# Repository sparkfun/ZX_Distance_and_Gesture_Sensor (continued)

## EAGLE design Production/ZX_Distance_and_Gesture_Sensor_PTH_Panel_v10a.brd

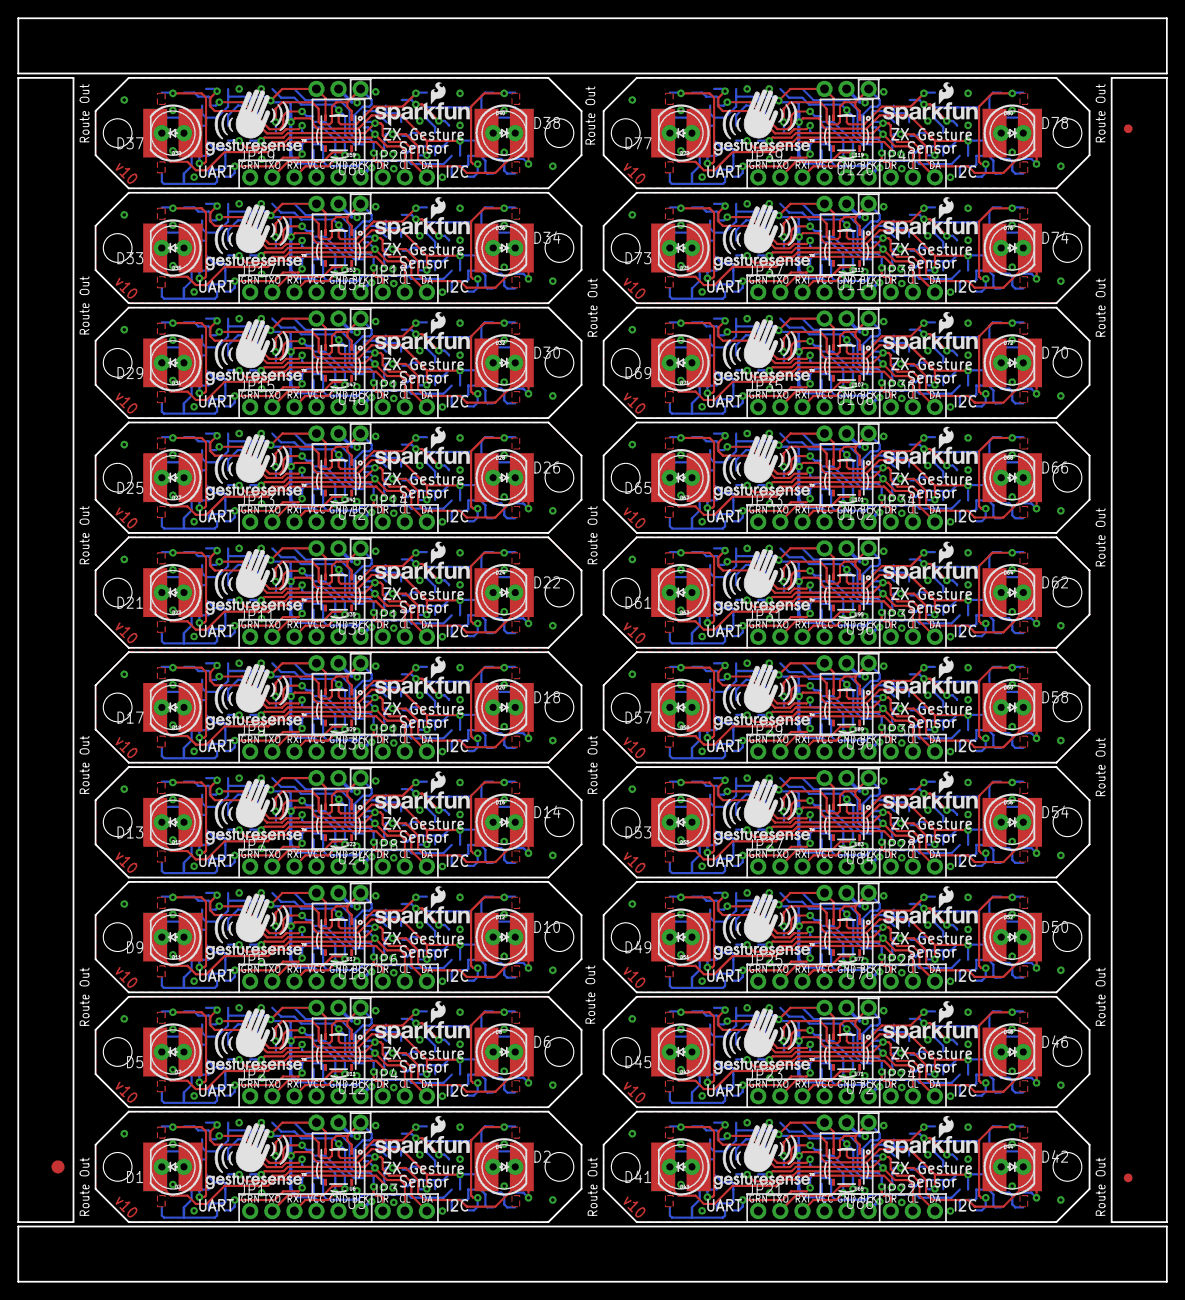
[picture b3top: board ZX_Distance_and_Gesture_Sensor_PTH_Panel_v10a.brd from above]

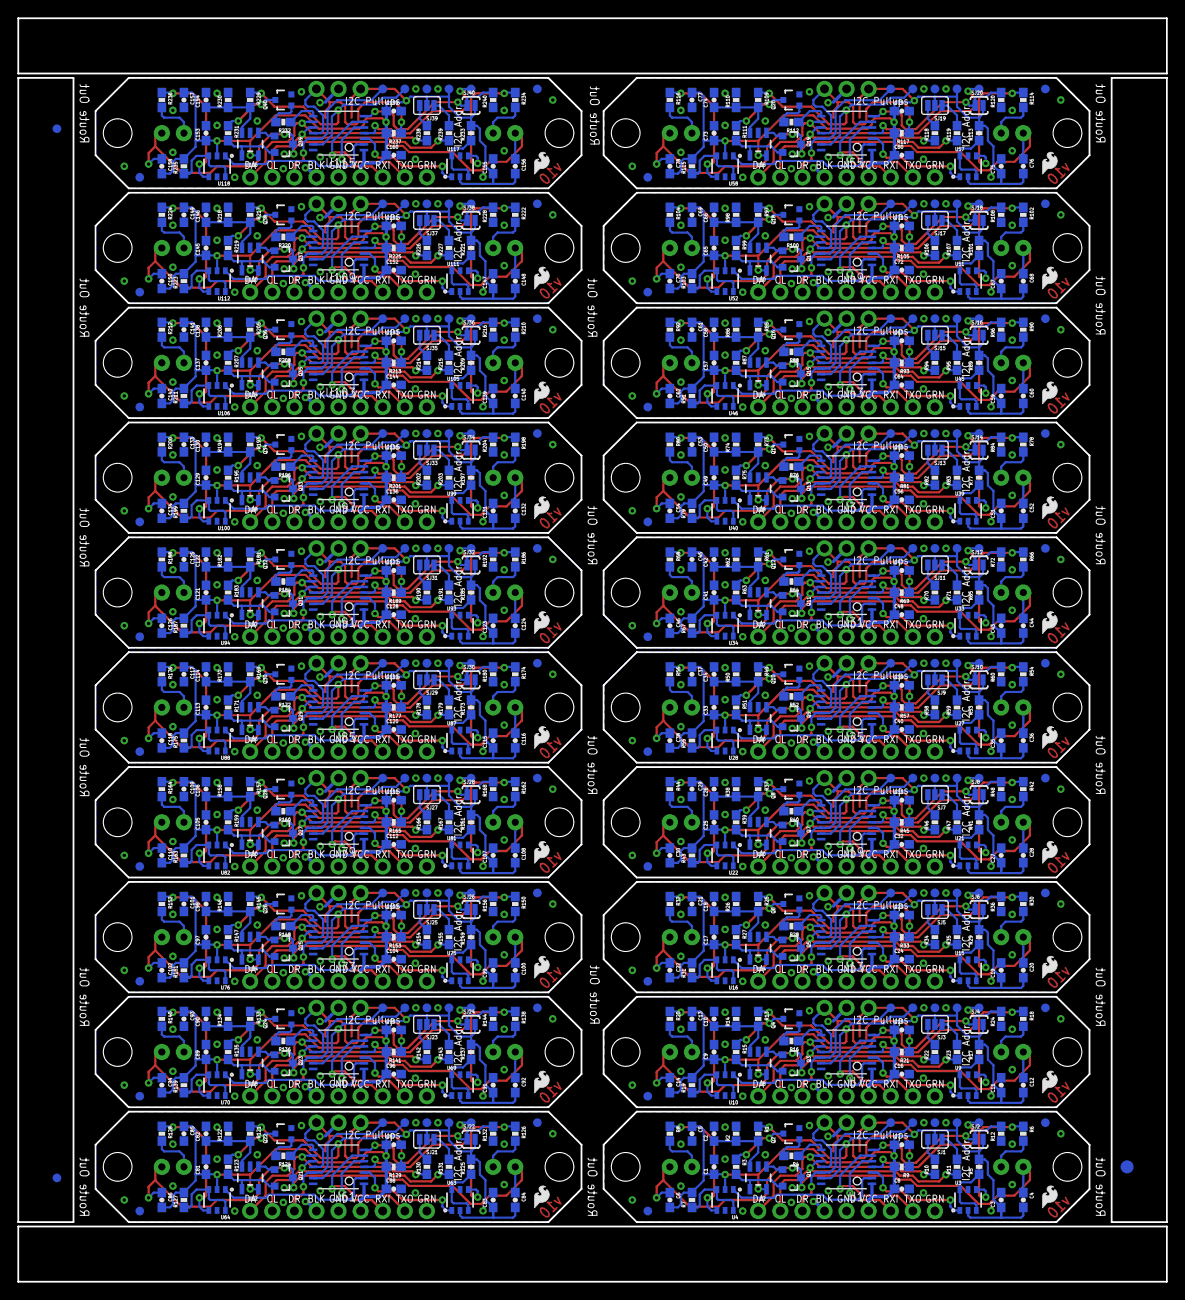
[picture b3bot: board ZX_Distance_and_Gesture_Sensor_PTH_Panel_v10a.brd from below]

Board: 2 copper layers, 132.1 x 145.3 mm, 966 parts (723 on the bottom side), 560 nets.

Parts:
C1, C3, C5, C8, C9, C11, C13, C16, C17, C19, C21, C24, C25, C27, C29, C32, C33, C35, C37, C40, C41, C43, C45, C48, C49, C51, C53, C56, C57, C59, C61, C64, C65, C67, C69, C72, C73, C75, C77, C80, C81, C83, C85, C88, C89, C91, C93, C96, C97, C99, C101, C104, C105, C107, C109, C112, C113, C115, C117, C120, C121, C123, C125, C128, C129, C131, C133, C136, C137, C139, C141, C144, C145, C147, C149, C152, C153, C155, C157, C160: 0.1uF; 0603-CAP
C2, C10, C18, C26, C34, C42, C50, C58, C66, C74, C82, C90, C98, C106, C114, C122, C130, C138, C146, C154: DNP; 0603-CAP
C4, C6, C12, C14, C20, C22, C28, C30, C36, C38, C44, C46, C52, C54, C60, C62, C68, C70, C76, C78, C84, C86, C92, C94, C100, C102, C108, C110, C116, C118, C124, C126, C132, C134, C140, C142, C148, C150, C156, C158: 10nF; 0603-CAP
C7, C15, C23, C31, C39, C47, C55, C63, C71, C79, C87, C95, C103, C111, C119, C127, C135, C143, C151, C159: 4.7uF; 0603-CAP
D1, D2, D5, D6, D9, D10, D13, D14, D17, D18, D21, D22, D25, D26, D29, D30, D33, D34, D37, D38, D41, D42, D45, D46, D49, D50, D53, D54, D57, D58, D61, D62, D65, D66, D69, D70, D73, D74, D77, D78: LED-IR-THRUTSAL6100; LED5MM
D3, D4, D7, D8, D11, D12, D15, D16, D19, D20, D23, D24, D27, D28, D31, D32, D35, D36, D39, D40, D43, D44, D47, D48, D51, D52, D55, D56, D59, D60, D63, D64, D67, D68, D71, D72, D75, D76, D79, D80: SFH4641SHORT2; SFH4641-SHORT2
E$1, E$3: FIDUCIAL-1.5X3
E$2, E$4, E$5, E$6: FIDUCIAL-1X2
FID1, FID2, FID3, FID4, FID5, FID6, FID7, FID8, FID9, FID10, FID11, FID12, FID13, FID14, FID15, FID16, FID17, FID18, FID19, FID20, FID21, FID22, FID23, FID24, FID25, FID26, FID27, FID28, FID29, FID30, FID31, FID32, FID33, FID34, FID35, FID36, FID37, FID38, FID39, FID40: FIDUCIAL1X2; FIDUCIAL-1X2
JP1, JP2, JP5, JP7, JP9, JP11, JP13, JP15, JP17, JP19, JP21, JP23, JP25, JP27, JP29, JP31, JP33, JP35, JP37, JP39: 1X06_NO_SILK
JP3, JP4, JP6, JP8, JP10, JP12, JP14, JP16, JP18, JP20, JP22, JP24, JP26, JP28, JP30, JP32, JP34, JP36, JP38, JP40: 1X03_NO_SILK
LOGO1, LOGO2, LOGO3, LOGO4, LOGO5, LOGO6, LOGO7, LOGO8, LOGO9, LOGO10, LOGO11, LOGO12, LOGO13, LOGO14, LOGO15, LOGO16, LOGO17, LOGO18, LOGO19, LOGO20: SFE_LOGO_FLAME.1_INCH; SFE_LOGO_FLAME_.1
Q1, Q3, Q5, Q7, Q9, Q11, Q13, Q15, Q17, Q19, Q21, Q23, Q25, Q27, Q29, Q31, Q33, Q35, Q37, Q39: MMBT2222A; SOT23-3
Q2, Q4, Q6, Q8, Q10, Q12, Q14, Q16, Q18, Q20, Q22, Q24, Q26, Q28, Q30, Q32, Q34, Q36, Q38, Q40: MOSFET-NCHANNEL2N7002PW; SOT323
R1, R2, R5, R7, R13, R14, R17, R19, R25, R26, R29, R31, R37, R38, R41, R43, R49, R50, R53, R55, R61, R62, R65, R67, R73, R74, R77, R79, R85, R86, R89, R91, R97, R98, R101, R103, R109, R110, R113, R115, R121, R122, R125, R127, R133, R134, R137, R139, R145, R146, R149, R151, R157, R158, R161, R163, R169, R170, R173, R175, R181, R182, R185, R187, R193, R194, R197, R199, R205, R206, R209, R211, R217, R218, R221, R223, R229, R230, R233, R235: 100k; 0603-RES
R3, R15, R27, R39, R51, R63, R75, R87, R99, R111, R123, R135, R147, R159, R171, R183, R195, R207, R219, R231: 10; 0603-RES
R4, R9, R16, R21, R28, R33, R40, R45, R52, R57, R64, R69, R76, R81, R88, R93, R100, R105, R112, R117, R124, R129, R136, R141, R148, R153, R160, R165, R172, R177, R184, R189, R196, R201, R208, R213, R220, R225, R232, R237: 1K; 0603-RES
R6, R8, R18, R20, R30, R32, R42, R44, R54, R56, R66, R68, R78, R80, R90, R92, R102, R104, R114, R116, R126, R128, R138, R140, R150, R152, R162, R164, R174, R176, R186, R188, R198, R200, R210, R212, R222, R224, R234, R236: 1; 0603-RES
R10, R11, R22, R23, R34, R35, R46, R47, R58, R59, R70, R71, R82, R83, R94, R95, R106, R107, R118, R119, R130, R131, R142, R143, R154, R155, R166, R167, R178, R179, R190, R191, R202, R203, R214, R215, R226, R227, R238, R239: 4.7K; 0603-RES
R12, R24, R36, R48, R60, R72, R84, R96, R108, R120, R132, R144, R156, R168, R180, R192, R204, R216, R228, R240: 10K; 0603-RES
SJ1, SJ3, SJ5, SJ7, SJ9, SJ11, SJ13, SJ15, SJ17, SJ19, SJ21, SJ23, SJ25, SJ27, SJ29, SJ31, SJ33, SJ35, SJ37, SJ39: JUMPER-PAD-3-NC_BY_PASTE; PAD-JUMPER-3-NC_BY_PASTE_YES_SILK_FULL_BOX
SJ2, SJ4, SJ6, SJ8, SJ10, SJ12, SJ14, SJ16, SJ18, SJ20, SJ22, SJ24, SJ26, SJ28, SJ30, SJ32, SJ34, SJ36, SJ38, SJ40: JUMPER-PAD-2-NOYES_SILK; PAD-JUMPER-2-NO_YES_SILK
STANDOFF1, STANDOFF2, STANDOFF3, STANDOFF4, STANDOFF5, STANDOFF6, STANDOFF7, STANDOFF8, STANDOFF9, STANDOFF10, STANDOFF11, STANDOFF12, STANDOFF13, STANDOFF14, STANDOFF15, STANDOFF16, STANDOFF17, STANDOFF18, STANDOFF19, STANDOFF20, STANDOFF21, STANDOFF22, STANDOFF23, STANDOFF24, STANDOFF25, STANDOFF26, STANDOFF27, STANDOFF28, STANDOFF29, STANDOFF30, STANDOFF31, STANDOFF32, STANDOFF33, STANDOFF34, STANDOFF35, STANDOFF36, STANDOFF37, STANDOFF38, STANDOFF39, STANDOFF40: STAND-OFF
TP1, TP2, TP3, TP4, TP5, TP6, TP7, TP8, TP9, TP10, TP11, TP12, TP13, TP14, TP15, TP16, TP17, TP18, TP19, TP20, TP21, TP22, TP23, TP24, TP25, TP26, TP27, TP28, TP29, TP30, TP31, TP32, TP33, TP34, TP35, TP36, TP37, TP38, TP39, TP40, TP41, TP42, TP43, TP44, TP45, TP46, TP47, TP48, TP49, TP50, TP51, TP52, TP53, TP54, TP55, TP56, TP57, TP58, TP59, TP60, TP61, TP62, TP63, TP64, TP65, TP66, TP67, TP68, TP69, TP70, TP71, TP72, TP73, TP74, TP75, TP76, TP77, TP78, TP79, TP80, TP81, TP82, TP83, TP84, TP85, TP86, TP87, TP88, TP89, TP90, TP91, TP92, TP93, TP94, TP95, TP96, TP97, TP98, TP99, TP100: TEST-POINT3X4; PAD.03X.04
U1, U7, U13, U19, U25, U31, U37, U43, U49, U55, U61, U67, U73, U79, U85, U91, U97, U103, U109, U115: PIC16F1823-14PINTSSOP; TSSOP14
U2, U8, U14, U20, U26, U32, U38, U44, U50, U56, U62, U68, U74, U80, U86, U92, U98, U104, U110, U116: MCP6021T-E/OT; SOT23-5
U3, U4, U9, U10, U15, U16, U21, U22, U27, U28, U33, U34, U39, U40, U45, U46, U51, U52, U57, U58, U63, U64, U69, U70, U75, U76, U81, U82, U87, U88, U93, U94, U99, U100, U105, U106, U111, U112, U117, U118: DMC2700UDM; SOT26
U5, U12, U18, U24, U30, U36, U42, U48, U54, U60, U66, U72, U78, U84, U90, U96, U102, U108, U114, U120: BRM-2A18VERT; BRM-2508_VERT
U6, U11, U17, U23, U29, U35, U41, U47, U53, U59, U65, U71, U77, U83, U89, U95, U101, U107, U113, U119: TSOP57238TT1; TSOP572
U$1, U$3, U$5, U$7, U$9, U$11, U$13, U$15, U$17, U$19, U$21, U$23, U$25, U$27, U$29, U$31, U$33, U$35, U$37, U$39: SFE_LOGO_NAME_FLAME.1_INCH; SFE_LOGO_NAME_FLAME_.1
U$2, U$4, U$6, U$8, U$10, U$12, U$14, U$16, U$18, U$20, U$22, U$24, U$26, U$28, U$30, U$32, U$34, U$36, U$38, U$40: GESTURESENSE_LOGOSTEXT; GESTURESENSE_TEXT

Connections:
CARRIER: R4.1, U1.8
CARRIER1: R16.1, U7.8
CARRIER2: R28.1, U13.8
CARRIER3: R40.1, U19.8
CARRIER4: R52.1, U25.8
CARRIER5: R64.1, U31.8
CARRIER6: R76.1, U37.8
CARRIER7: R88.1, U43.8
CARRIER8: R100.1, U49.8
CARRIER9: R112.1, U55.8
CARRIER10: R124.1, U61.8
CARRIER11: R136.1, U67.8
CARRIER12: R148.1, U73.8
CARRIER13: R160.1, U79.8
CARRIER14: R172.1, U85.8
CARRIER15: R184.1, U91.8
CARRIER16: R196.1, U97.8
CARRIER17: R208.1, U103.8
CARRIER18: R220.1, U109.8
CARRIER19: R232.1, U115.8
COMMON: C4.1, C6.1, D1.K, D2.K, D3.C, D4.C, Q1.3
COMMON1: C12.1, C14.1, D5.K, D6.K, D7.C, D8.C, Q3.3
COMMON2: C20.1, C22.1, D9.K, D10.K, D11.C, D12.C, Q5.3
COMMON3: C28.1, C30.1, D13.K, D14.K, D15.C, D16.C, Q7.3
COMMON4: C36.1, C38.1, D17.K, D18.K, D19.C, D20.C, Q9.3
COMMON5: C44.1, C46.1, D21.K, D22.K, D23.C, D24.C, Q11.3
COMMON6: C52.1, C54.1, D25.K, D26.K, D27.C, D28.C, Q13.3
COMMON7: C60.1, C62.1, D29.K, D30.K, D31.C, D32.C, Q15.3
COMMON8: C68.1, C70.1, D33.K, D34.K, D35.C, D36.C, Q17.3
COMMON9: C76.1, C78.1, D37.K, D38.K, D39.C, D40.C, Q19.3
COMMON10: C84.1, C86.1, D41.K, D42.K, D43.C, D44.C, Q21.3
COMMON11: C92.1, C94.1, D45.K, D46.K, D47.C, D48.C, Q23.3
COMMON12: C100.1, C102.1, D49.K, D50.K, D51.C, D52.C, Q25.3
COMMON13: C108.1, C110.1, D53.K, D54.K, D55.C, D56.C, Q27.3
COMMON14: C116.1, C118.1, D57.K, D58.K, D59.C, D60.C, Q29.3
COMMON15: C124.1, C126.1, D61.K, D62.K, D63.C, D64.C, Q31.3
COMMON16: C132.1, C134.1, D65.K, D66.K, D67.C, D68.C, Q33.3
COMMON17: C140.1, C142.1, D69.K, D70.K, D71.C, D72.C, Q35.3
COMMON18: C148.1, C150.1, D73.K, D74.K, D75.C, D76.C, Q37.3
COMMON19: C156.1, C158.1, D77.K, D78.K, D79.C, D80.C, Q39.3
EM1: U1.3, U3.G1
EM2: U1.2, U4.G1
EM3: U7.3, U9.G1
EM4: U7.2, U10.G1
EM5: U13.3, U15.G1
EM6: U13.2, U16.G1
EM7: U19.3, U21.G1
EM8: U19.2, U22.G1
EM9: U25.3, U27.G1
EM10: U25.2, U28.G1
EM11: U31.3, U33.G1
EM12: U31.2, U34.G1
EM13: U37.3, U39.G1
EM14: U37.2, U40.G1
EM15: U43.3, U45.G1
EM16: U43.2, U46.G1
EM17: U49.3, U51.G1
EM18: U49.2, U52.G1
EM19: U55.3, U57.G1
EM20: U55.2, U58.G1
EM21: U61.3, U63.G1
EM22: U61.2, U64.G1
EM23: U67.3, U69.G1
EM24: U67.2, U70.G1
EM25: U73.3, U75.G1
EM26: U73.2, U76.G1
EM27: U79.3, U81.G1
EM28: U79.2, U82.G1
EM29: U85.3, U87.G1
EM30: U85.2, U88.G1
EM31: U91.3, U93.G1
EM32: U91.2, U94.G1
EM33: U97.3, U99.G1
EM34: U97.2, U100.G1
EM35: U103.3, U105.G1
EM36: U103.2, U106.G1
EM37: U109.3, U111.G1
EM38: U109.2, U112.G1
EM39: U115.3, U117.G1
EM40: U115.2, U118.G1
GND: C1.2, C2.2, C3.2, C5.2, C7.2, C8.2, JP1.5, JP1.6, Q2.2, R2.2, R12.1, TP2.P$1, U1.14, U2.2, U3.S1, U4.S1, U5.2, U6.6, U6.8
GND1: C9.2, C10.2, C11.2, C13.2, C15.2, C16.2, JP2.5, JP2.6, Q4.2, R14.2, R24.1, TP7.P$1, U7.14, U8.2, U9.S1, U10.S1, U11.6, U11.8, U12.2
GND2: C17.2, C18.2, C19.2, C21.2, C23.2, C24.2, JP5.5, JP5.6, Q6.2, R26.2, R36.1, TP12.P$1, U13.14, U14.2, U15.S1, U16.S1, U17.6, U17.8, U18.2
GND3: C25.2, C26.2, C27.2, C29.2, C31.2, C32.2, JP7.5, JP7.6, Q8.2, R38.2, R48.1, TP17.P$1, U19.14, U20.2, U21.S1, U22.S1, U23.6, U23.8, U24.2
GND4: C33.2, C34.2, C35.2, C37.2, C39.2, C40.2, JP9.5, JP9.6, Q10.2, R50.2, R60.1, TP22.P$1, U25.14, U26.2, U27.S1, U28.S1, U29.6, U29.8, U30.2
GND5: C41.2, C42.2, C43.2, C45.2, C47.2, C48.2, JP11.5, JP11.6, Q12.2, R62.2, R72.1, TP27.P$1, U31.14, U32.2, U33.S1, U34.S1, U35.6, U35.8, U36.2
GND6: C49.2, C50.2, C51.2, C53.2, C55.2, C56.2, JP13.5, JP13.6, Q14.2, R74.2, R84.1, TP32.P$1, U37.14, U38.2, U39.S1, U40.S1, U41.6, U41.8, U42.2
GND7: C57.2, C58.2, C59.2, C61.2, C63.2, C64.2, JP15.5, JP15.6, Q16.2, R86.2, R96.1, TP37.P$1, U43.14, U44.2, U45.S1, U46.S1, U47.6, U47.8, U48.2
GND8: C65.2, C66.2, C67.2, C69.2, C71.2, C72.2, JP17.5, JP17.6, Q18.2, R98.2, R108.1, TP42.P$1, U49.14, U50.2, U51.S1, U52.S1, U53.6, U53.8, U54.2
GND9: C73.2, C74.2, C75.2, C77.2, C79.2, C80.2, JP19.5, JP19.6, Q20.2, R110.2, R120.1, TP47.P$1, U55.14, U56.2, U57.S1, U58.S1, U59.6, U59.8, U60.2
GND10: C81.2, C82.2, C83.2, C85.2, C87.2, C88.2, JP21.5, JP21.6, Q22.2, R122.2, R132.1, TP52.P$1, U61.14, U62.2, U63.S1, U64.S1, U65.6, U65.8, U66.2
GND11: C89.2, C90.2, C91.2, C93.2, C95.2, C96.2, JP23.5, JP23.6, Q24.2, R134.2, R144.1, TP57.P$1, U67.14, U68.2, U69.S1, U70.S1, U71.6, U71.8, U72.2
GND12: C97.2, C98.2, C99.2, C101.2, C103.2, C104.2, JP25.5, JP25.6, Q26.2, R146.2, R156.1, TP62.P$1, U73.14, U74.2, U75.S1, U76.S1, U77.6, U77.8, U78.2
GND13: C105.2, C106.2, C107.2, C109.2, C111.2, C112.2, JP27.5, JP27.6, Q28.2, R158.2, R168.1, TP67.P$1, U79.14, U80.2, U81.S1, U82.S1, U83.6, U83.8, U84.2
GND14: C113.2, C114.2, C115.2, C117.2, C119.2, C120.2, JP29.5, JP29.6, Q30.2, R170.2, R180.1, TP72.P$1, U85.14, U86.2, U87.S1, U88.S1, U89.6, U89.8, U90.2
GND15: C121.2, C122.2, C123.2, C125.2, C127.2, C128.2, JP31.5, JP31.6, Q32.2, R182.2, R192.1, TP77.P$1, U91.14, U92.2, U93.S1, U94.S1, U95.6, U95.8, U96.2
GND16: C129.2, C130.2, C131.2, C133.2, C135.2, C136.2, JP33.5, JP33.6, Q34.2, R194.2, R204.1, TP82.P$1, U97.14, U98.2, U99.S1, U100.S1, U101.6, U101.8, U102.2
GND17: C137.2, C138.2, C139.2, C141.2, C143.2, C144.2, JP35.5, JP35.6, Q36.2, R206.2, R216.1, TP87.P$1, U103.14, U104.2, U105.S1, U106.S1, U107.6, U107.8, U108.2
GND18: C145.2, C146.2, C147.2, C149.2, C151.2, C152.2, JP37.5, JP37.6, Q38.2, R218.2, R228.1, TP92.P$1, U109.14, U110.2, U111.S1, U112.S1, U113.6, U113.8, U114.2
GND19: C153.2, C154.2, C155.2, C157.2, C159.2, C160.2, JP39.5, JP39.6, Q40.2, R230.2, R240.1, TP97.P$1, U115.14, U116.2, U117.S1, U118.S1, U119.6, U119.8, U120.2
I2C_ADDR: R12.2, SJ2.1, U1.7
I2C_ADDR1: R24.2, SJ4.1, U7.7
I2C_ADDR2: R36.2, SJ6.1, U13.7
I2C_ADDR3: R48.2, SJ8.1, U19.7
I2C_ADDR4: R60.2, SJ10.1, U25.7
I2C_ADDR5: R72.2, SJ12.1, U31.7
I2C_ADDR6: R84.2, SJ14.1, U37.7
I2C_ADDR7: R96.2, SJ16.1, U43.7
I2C_ADDR8: R108.2, SJ18.1, U49.7
I2C_ADDR9: R120.2, SJ20.1, U55.7
I2C_ADDR10: R132.2, SJ22.1, U61.7
I2C_ADDR11: R144.2, SJ24.1, U67.7
I2C_ADDR12: R156.2, SJ26.1, U73.7
I2C_ADDR13: R168.2, SJ28.1, U79.7
I2C_ADDR14: R180.2, SJ30.1, U85.7
I2C_ADDR15: R192.2, SJ32.1, U91.7
I2C_ADDR16: R204.2, SJ34.1, U97.7
I2C_ADDR17: R216.2, SJ36.1, U103.7
I2C_ADDR18: R228.2, SJ38.1, U109.7
I2C_ADDR19: R240.2, SJ40.1, U115.7
I2C_SCL: JP3.2, R11.1, U1.10
I2C_SCL1: JP4.2, R23.1, U7.10
I2C_SCL2: JP6.2, R35.1, U13.10
I2C_SCL3: JP8.2, R47.1, U19.10
I2C_SCL4: JP10.2, R59.1, U25.10
I2C_SCL5: JP12.2, R71.1, U31.10
I2C_SCL6: JP14.2, R83.1, U37.10
I2C_SCL7: JP16.2, R95.1, U43.10
I2C_SCL8: JP18.2, R107.1, U49.10
I2C_SCL9: JP20.2, R119.1, U55.10
I2C_SCL10: JP22.2, R131.1, U61.10
I2C_SCL11: JP24.2, R143.1, U67.10
I2C_SCL12: JP26.2, R155.1, U73.10
I2C_SCL13: JP28.2, R167.1, U79.10
I2C_SCL14: JP30.2, R179.1, U85.10
I2C_SCL15: JP32.2, R191.1, U91.10
I2C_SCL16: JP34.2, R203.1, U97.10
I2C_SCL17: JP36.2, R215.1, U103.10
I2C_SCL18: JP38.2, R227.1, U109.10
I2C_SCL19: JP40.2, R239.1, U115.10
I2C_SDA: JP3.3, R10.1, U1.9
I2C_SDA1: JP4.3, R22.1, U7.9
I2C_SDA2: JP6.3, R34.1, U13.9
I2C_SDA3: JP8.3, R46.1, U19.9
I2C_SDA4: JP10.3, R58.1, U25.9
I2C_SDA5: JP12.3, R70.1, U31.9
I2C_SDA6: JP14.3, R82.1, U37.9
I2C_SDA7: JP16.3, R94.1, U43.9
I2C_SDA8: JP18.3, R106.1, U49.9
I2C_SDA9: JP20.3, R118.1, U55.9
I2C_SDA10: JP22.3, R130.1, U61.9
I2C_SDA11: JP24.3, R142.1, U67.9
I2C_SDA12: JP26.3, R154.1, U73.9
I2C_SDA13: JP28.3, R166.1, U79.9
I2C_SDA14: JP30.3, R178.1, U85.9
I2C_SDA15: JP32.3, R190.1, U91.9
I2C_SDA16: JP34.3, R202.1, U97.9
I2C_SDA17: JP36.3, R214.1, U103.9
I2C_SDA18: JP38.3, R226.1, U109.9
I2C_SDA19: JP40.3, R238.1, U115.9
ICSPCLK/DATA_RDY: JP3.1, TP4.P$1, U1.12
ICSPCLK/DATA_RDY1: JP4.1, TP9.P$1, U7.12
ICSPCLK/DATA_RDY2: JP6.1, TP14.P$1, U13.12
ICSPCLK/DATA_RDY3: JP8.1, TP19.P$1, U19.12
ICSPCLK/DATA_RDY4: JP10.1, TP24.P$1, U25.12
ICSPCLK/DATA_RDY5: JP12.1, TP29.P$1, U31.12
ICSPCLK/DATA_RDY6: JP14.1, TP34.P$1, U37.12
ICSPCLK/DATA_RDY7: JP16.1, TP39.P$1, U43.12
ICSPCLK/DATA_RDY8: JP18.1, TP44.P$1, U49.12
ICSPCLK/DATA_RDY9: JP20.1, TP49.P$1, U55.12
ICSPCLK/DATA_RDY10: JP22.1, TP54.P$1, U61.12
ICSPCLK/DATA_RDY11: JP24.1, TP59.P$1, U67.12
ICSPCLK/DATA_RDY12: JP26.1, TP64.P$1, U73.12
ICSPCLK/DATA_RDY13: JP28.1, TP69.P$1, U79.12
ICSPCLK/DATA_RDY14: JP30.1, TP74.P$1, U85.12
ICSPCLK/DATA_RDY15: JP32.1, TP79.P$1, U91.12
ICSPCLK/DATA_RDY16: JP34.1, TP84.P$1, U97.12
ICSPCLK/DATA_RDY17: JP36.1, TP89.P$1, U103.12
ICSPCLK/DATA_RDY18: JP38.1, TP94.P$1, U109.12
ICSPCLK/DATA_RDY19: JP40.1, TP99.P$1, U115.12
ICSPDAT/DACOUT: R1.1, TP5.P$1, U1.13
ICSPDAT/DACOUT1: R13.1, TP10.P$1, U7.13
ICSPDAT/DACOUT2: R25.1, TP15.P$1, U13.13
ICSPDAT/DACOUT3: R37.1, TP20.P$1, U19.13
ICSPDAT/DACOUT4: R49.1, TP25.P$1, U25.13
ICSPDAT/DACOUT5: R61.1, TP30.P$1, U31.13
ICSPDAT/DACOUT6: R73.1, TP35.P$1, U37.13
ICSPDAT/DACOUT7: R85.1, TP40.P$1, U43.13
ICSPDAT/DACOUT8: R97.1, TP45.P$1, U49.13
ICSPDAT/DACOUT9: R109.1, TP50.P$1, U55.13
ICSPDAT/DACOUT10: R121.1, TP55.P$1, U61.13
ICSPDAT/DACOUT11: R133.1, TP60.P$1, U67.13
ICSPDAT/DACOUT12: R145.1, TP65.P$1, U73.13
ICSPDAT/DACOUT13: R157.1, TP70.P$1, U79.13
ICSPDAT/DACOUT14: R169.1, TP75.P$1, U85.13
ICSPDAT/DACOUT15: R181.1, TP80.P$1, U91.13
ICSPDAT/DACOUT16: R193.1, TP85.P$1, U97.13
ICSPDAT/DACOUT17: R205.1, TP90.P$1, U103.13
ICSPDAT/DACOUT18: R217.1, TP95.P$1, U109.13
ICSPDAT/DACOUT19: R229.1, TP100.P$1, U115.13
MCLR: TP3.P$1, U1.4
MCLR1: TP8.P$1, U7.4
MCLR2: TP13.P$1, U13.4
MCLR3: TP18.P$1, U19.4
MCLR4: TP23.P$1, U25.4
MCLR5: TP28.P$1, U31.4
MCLR6: TP33.P$1, U37.4
MCLR7: TP38.P$1, U43.4
MCLR8: TP43.P$1, U49.4
MCLR9: TP48.P$1, U55.4
MCLR10: TP53.P$1, U61.4
MCLR11: TP58.P$1, U67.4
MCLR12: TP63.P$1, U73.4
MCLR13: TP68.P$1, U79.4
MCLR14: TP73.P$1, U85.4
MCLR15: TP78.P$1, U91.4
MCLR16: TP83.P$1, U97.4
MCLR17: TP88.P$1, U103.4
MCLR18: TP93.P$1, U109.4
MCLR19: TP98.P$1, U115.4
unnamed: C2.1, R1.2, R2.1, U2.3
unnamed: Q1.2, R3.2, U2.4
unnamed: Q1.1, U2.1
unnamed: Q2.3, R3.1
unnamed: Q2.1, R4.2
unnamed: R6.1, U3.D2
unnamed: D1.A, D3.A, R6.2
unnamed: R5.1, U3.D1, U3.G2
unnamed: R7.1, U4.D1, U4.G2
unnamed: R10.2, SJ1.3
unnamed: R8.1, U4.D2
unnamed: D2.A, D4.A, R8.2
unnamed: R11.2, SJ1.1
unnamed: C10.1, R13.2, R14.1, U8.3
unnamed: Q3.1, U8.1
unnamed: Q4.3, R15.1
unnamed: Q4.1, R16.2
unnamed: Q3.2, R15.2, U8.4
unnamed: R18.1, U9.D2
unnamed: D5.A, D7.A, R18.2
unnamed: R17.1, U9.D1, U9.G2
unnamed: R19.1, U10.D1, U10.G2
unnamed: R20.1, U10.D2
unnamed: D6.A, D8.A, R20.2
unnamed: R22.2, SJ3.3
unnamed: R23.2, SJ3.1
unnamed: C18.1, R25.2, R26.1, U14.3
unnamed: Q5.1, U14.1
unnamed: Q6.3, R27.1
unnamed: Q6.1, R28.2
unnamed: Q5.2, R27.2, U14.4
unnamed: R30.1, U15.D2
unnamed: D9.A, D11.A, R30.2
unnamed: R29.1, U15.D1, U15.G2
unnamed: R31.1, U16.D1, U16.G2
unnamed: R32.1, U16.D2
unnamed: D10.A, D12.A, R32.2
unnamed: R34.2, SJ5.3
unnamed: R35.2, SJ5.1
unnamed: C26.1, R37.2, R38.1, U20.3
unnamed: Q7.1, U20.1
unnamed: Q8.3, R39.1
unnamed: Q8.1, R40.2
unnamed: Q7.2, R39.2, U20.4
unnamed: R42.1, U21.D2
unnamed: D13.A, D15.A, R42.2
unnamed: R41.1, U21.D1, U21.G2
unnamed: R43.1, U22.D1, U22.G2
unnamed: R44.1, U22.D2
unnamed: D14.A, D16.A, R44.2
unnamed: R46.2, SJ7.3
unnamed: R47.2, SJ7.1
unnamed: C34.1, R49.2, R50.1, U26.3
unnamed: Q9.1, U26.1
unnamed: Q10.3, R51.1
unnamed: Q10.1, R52.2
unnamed: Q9.2, R51.2, U26.4
unnamed: R54.1, U27.D2
unnamed: D17.A, D19.A, R54.2
unnamed: R53.1, U27.D1, U27.G2
unnamed: R55.1, U28.D1, U28.G2
unnamed: R56.1, U28.D2
unnamed: D18.A, D20.A, R56.2
unnamed: R58.2, SJ9.3
unnamed: R59.2, SJ9.1
unnamed: C42.1, R61.2, R62.1, U32.3
unnamed: Q11.1, U32.1
unnamed: Q12.3, R63.1
unnamed: Q12.1, R64.2
unnamed: Q11.2, R63.2, U32.4
unnamed: R66.1, U33.D2
unnamed: D21.A, D23.A, R66.2
unnamed: R65.1, U33.D1, U33.G2
unnamed: R67.1, U34.D1, U34.G2
unnamed: R68.1, U34.D2
unnamed: D22.A, D24.A, R68.2
unnamed: R70.2, SJ11.3
unnamed: R71.2, SJ11.1
unnamed: C50.1, R73.2, R74.1, U38.3
unnamed: Q13.1, U38.1
unnamed: Q14.3, R75.1
unnamed: Q14.1, R76.2
unnamed: Q13.2, R75.2, U38.4
unnamed: R78.1, U39.D2
unnamed: D25.A, D27.A, R78.2
unnamed: R77.1, U39.D1, U39.G2
unnamed: R79.1, U40.D1, U40.G2
unnamed: R80.1, U40.D2
unnamed: D26.A, D28.A, R80.2
unnamed: R82.2, SJ13.3
unnamed: R83.2, SJ13.1
unnamed: C58.1, R85.2, R86.1, U44.3
unnamed: Q15.1, U44.1
unnamed: Q16.3, R87.1
unnamed: Q16.1, R88.2
unnamed: Q15.2, R87.2, U44.4
unnamed: R90.1, U45.D2
unnamed: D29.A, D31.A, R90.2
unnamed: R89.1, U45.D1, U45.G2
unnamed: R91.1, U46.D1, U46.G2
unnamed: R92.1, U46.D2
unnamed: D30.A, D32.A, R92.2
unnamed: R94.2, SJ15.3
unnamed: R95.2, SJ15.1
unnamed: C66.1, R97.2, R98.1, U50.3
unnamed: Q17.1, U50.1
unnamed: Q18.3, R99.1
unnamed: Q18.1, R100.2
unnamed: Q17.2, R99.2, U50.4
unnamed: R102.1, U51.D2
unnamed: D33.A, D35.A, R102.2
unnamed: R101.1, U51.D1, U51.G2
unnamed: R103.1, U52.D1, U52.G2
unnamed: R104.1, U52.D2
unnamed: D34.A, D36.A, R104.2
unnamed: R106.2, SJ17.3
unnamed: R107.2, SJ17.1
unnamed: C74.1, R109.2, R110.1, U56.3
unnamed: Q19.1, U56.1
unnamed: Q20.3, R111.1
unnamed: Q20.1, R112.2
unnamed: Q19.2, R111.2, U56.4
unnamed: R114.1, U57.D2
unnamed: D37.A, D39.A, R114.2
unnamed: R113.1, U57.D1, U57.G2
unnamed: R115.1, U58.D1, U58.G2
unnamed: R116.1, U58.D2
unnamed: D38.A, D40.A, R116.2
unnamed: R118.2, SJ19.3
unnamed: R119.2, SJ19.1
unnamed: C82.1, R121.2, R122.1, U62.3
unnamed: Q21.1, U62.1
unnamed: Q22.3, R123.1
unnamed: Q22.1, R124.2
unnamed: Q21.2, R123.2, U62.4
unnamed: R126.1, U63.D2
unnamed: D41.A, D43.A, R126.2
unnamed: R125.1, U63.D1, U63.G2
unnamed: R127.1, U64.D1, U64.G2
unnamed: R128.1, U64.D2
unnamed: D42.A, D44.A, R128.2
unnamed: R130.2, SJ21.3
unnamed: R131.2, SJ21.1
unnamed: C90.1, R133.2, R134.1, U68.3
unnamed: Q23.1, U68.1
unnamed: Q24.3, R135.1
unnamed: Q24.1, R136.2
unnamed: Q23.2, R135.2, U68.4
unnamed: R138.1, U69.D2
unnamed: D45.A, D47.A, R138.2
unnamed: R137.1, U69.D1, U69.G2
unnamed: R139.1, U70.D1, U70.G2
unnamed: R140.1, U70.D2
unnamed: D46.A, D48.A, R140.2
unnamed: R142.2, SJ23.3
unnamed: R143.2, SJ23.1
unnamed: C98.1, R145.2, R146.1, U74.3
unnamed: Q25.1, U74.1
unnamed: Q26.3, R147.1
unnamed: Q26.1, R148.2
unnamed: Q25.2, R147.2, U74.4
unnamed: R150.1, U75.D2
unnamed: D49.A, D51.A, R150.2
unnamed: R149.1, U75.D1, U75.G2
unnamed: R151.1, U76.D1, U76.G2
unnamed: R152.1, U76.D2
unnamed: D50.A, D52.A, R152.2
unnamed: R154.2, SJ25.3
unnamed: R155.2, SJ25.1
unnamed: C106.1, R157.2, R158.1, U80.3
unnamed: Q27.1, U80.1
unnamed: Q28.3, R159.1
unnamed: Q28.1, R160.2
unnamed: Q27.2, R159.2, U80.4
unnamed: R162.1, U81.D2
unnamed: D53.A, D55.A, R162.2
unnamed: R161.1, U81.D1, U81.G2
unnamed: R163.1, U82.D1, U82.G2
unnamed: R164.1, U82.D2
unnamed: D54.A, D56.A, R164.2
unnamed: R166.2, SJ27.3
unnamed: R167.2, SJ27.1
unnamed: C114.1, R169.2, R170.1, U86.3
unnamed: Q29.1, U86.1
unnamed: Q30.3, R171.1
unnamed: Q30.1, R172.2
unnamed: Q29.2, R171.2, U86.4
unnamed: R174.1, U87.D2
unnamed: D57.A, D59.A, R174.2
unnamed: R173.1, U87.D1, U87.G2
unnamed: R175.1, U88.D1, U88.G2
unnamed: R176.1, U88.D2
unnamed: D58.A, D60.A, R176.2
unnamed: R178.2, SJ29.3
unnamed: R179.2, SJ29.1
unnamed: C122.1, R181.2, R182.1, U92.3
unnamed: Q31.1, U92.1
unnamed: Q32.3, R183.1
unnamed: Q32.1, R184.2
unnamed: Q31.2, R183.2, U92.4
unnamed: R186.1, U93.D2
unnamed: D61.A, D63.A, R186.2
unnamed: R185.1, U93.D1, U93.G2
unnamed: R187.1, U94.D1, U94.G2
unnamed: R188.1, U94.D2
unnamed: D62.A, D64.A, R188.2
unnamed: R190.2, SJ31.3
unnamed: R191.2, SJ31.1
unnamed: C130.1, R193.2, R194.1, U98.3
unnamed: Q33.1, U98.1
unnamed: Q34.3, R195.1
unnamed: Q34.1, R196.2
unnamed: Q33.2, R195.2, U98.4
unnamed: R198.1, U99.D2
unnamed: D65.A, D67.A, R198.2
unnamed: R197.1, U99.D1, U99.G2
unnamed: R199.1, U100.D1, U100.G2
unnamed: R200.1, U100.D2
unnamed: D66.A, D68.A, R200.2
unnamed: R202.2, SJ33.3
unnamed: R203.2, SJ33.1
unnamed: C138.1, R205.2, R206.1, U104.3
unnamed: Q35.1, U104.1
unnamed: Q36.3, R207.1
unnamed: Q36.1, R208.2
unnamed: Q35.2, R207.2, U104.4
unnamed: R210.1, U105.D2
unnamed: D69.A, D71.A, R210.2
unnamed: R209.1, U105.D1, U105.G2
unnamed: R211.1, U106.D1, U106.G2
unnamed: R212.1, U106.D2
unnamed: D70.A, D72.A, R212.2
unnamed: R214.2, SJ35.3
unnamed: R215.2, SJ35.1
unnamed: C146.1, R217.2, R218.1, U110.3
unnamed: Q37.1, U110.1
unnamed: Q38.3, R219.1
unnamed: Q38.1, R220.2
unnamed: Q37.2, R219.2, U110.4
unnamed: R222.1, U111.D2
unnamed: D73.A, D75.A, R222.2
unnamed: R221.1, U111.D1, U111.G2
unnamed: R223.1, U112.D1, U112.G2
unnamed: R224.1, U112.D2
unnamed: D74.A, D76.A, R224.2
unnamed: R226.2, SJ37.3
unnamed: R227.2, SJ37.1
unnamed: C154.1, R229.2, R230.1, U116.3
unnamed: Q39.1, U116.1
unnamed: Q40.3, R231.1
unnamed: Q40.1, R232.2
unnamed: Q39.2, R231.2, U116.4
unnamed: R234.1, U117.D2
unnamed: D77.A, D79.A, R234.2
unnamed: R233.1, U117.D1, U117.G2
unnamed: R235.1, U118.D1, U118.G2
unnamed: R236.1, U118.D2
unnamed: D78.A, D80.A, R236.2
unnamed: R238.2, SJ39.3
unnamed: R239.2, SJ39.1
RECEIVER: R9.1, U1.11, U5.1, U6.1
RECEIVER1: R21.1, U7.11, U11.1, U12.1
RECEIVER2: R33.1, U13.11, U17.1, U18.1
RECEIVER3: R45.1, U19.11, U23.1, U24.1
RECEIVER4: R57.1, U25.11, U29.1, U30.1
RECEIVER5: R69.1, U31.11, U35.1, U36.1
RECEIVER6: R81.1, U37.11, U41.1, U42.1
RECEIVER7: R93.1, U43.11, U47.1, U48.1
RECEIVER8: R105.1, U49.11, U53.1, U54.1
RECEIVER9: R117.1, U55.11, U59.1, U60.1
RECEIVER10: R129.1, U61.11, U65.1, U66.1
RECEIVER11: R141.1, U67.11, U71.1, U72.1
RECEIVER12: R153.1, U73.11, U77.1, U78.1
RECEIVER13: R165.1, U79.11, U83.1, U84.1
RECEIVER14: R177.1, U85.11, U89.1, U90.1
RECEIVER15: R189.1, U91.11, U95.1, U96.1
RECEIVER16: R201.1, U97.11, U101.1, U102.1
RECEIVER17: R213.1, U103.11, U107.1, U108.1
RECEIVER18: R225.1, U109.11, U113.1, U114.1
RECEIVER19: R237.1, U115.11, U119.1, U120.1
UART_RX: JP1.2, U1.6
UART_RX1: JP2.2, U7.6
UART_RX2: JP5.2, U13.6
UART_RX3: JP7.2, U19.6
UART_RX4: JP9.2, U25.6
UART_RX5: JP11.2, U31.6
UART_RX6: JP13.2, U37.6
UART_RX7: JP15.2, U43.6
UART_RX8: JP17.2, U49.6
UART_RX9: JP19.2, U55.6
UART_RX10: JP21.2, U61.6
UART_RX11: JP23.2, U67.6
UART_RX12: JP25.2, U73.6
UART_RX13: JP27.2, U79.6
UART_RX14: JP29.2, U85.6
UART_RX15: JP31.2, U91.6
UART_RX16: JP33.2, U97.6
UART_RX17: JP35.2, U103.6
UART_RX18: JP37.2, U109.6
UART_RX19: JP39.2, U115.6
UART_TX: JP1.3, U1.5
UART_TX1: JP2.3, U7.5
UART_TX2: JP5.3, U13.5
UART_TX3: JP7.3, U19.5
UART_TX4: JP9.3, U25.5
UART_TX5: JP11.3, U31.5
UART_TX6: JP13.3, U37.5
UART_TX7: JP15.3, U43.5
UART_TX8: JP17.3, U49.5
UART_TX9: JP19.3, U55.5
UART_TX10: JP21.3, U61.5
UART_TX11: JP23.3, U67.5
UART_TX12: JP25.3, U73.5
UART_TX13: JP27.3, U79.5
UART_TX14: JP29.3, U85.5
UART_TX15: JP31.3, U91.5
UART_TX16: JP33.3, U97.5
UART_TX17: JP35.3, U103.5
UART_TX18: JP37.3, U109.5
UART_TX19: JP39.3, U115.5
VCC: C1.1, C3.1, C4.2, C5.1, C6.2, C7.1, C8.1, JP1.4, R5.2, R7.2, R9.2, SJ1.2, SJ2.2, TP1.P$1, U1.1, U2.5, U3.S2, U4.S2, U5.3, U6.5
VCC1: C9.1, C11.1, C12.2, C13.1, C14.2, C15.1, C16.1, JP2.4, R17.2, R19.2, R21.2, SJ3.2, SJ4.2, TP6.P$1, U7.1, U8.5, U9.S2, U10.S2, U11.5, U12.3
VCC2: C17.1, C19.1, C20.2, C21.1, C22.2, C23.1, C24.1, JP5.4, R29.2, R31.2, R33.2, SJ5.2, SJ6.2, TP11.P$1, U13.1, U14.5, U15.S2, U16.S2, U17.5, U18.3
VCC3: C25.1, C27.1, C28.2, C29.1, C30.2, C31.1, C32.1, JP7.4, R41.2, R43.2, R45.2, SJ7.2, SJ8.2, TP16.P$1, U19.1, U20.5, U21.S2, U22.S2, U23.5, U24.3
VCC4: C33.1, C35.1, C36.2, C37.1, C38.2, C39.1, C40.1, JP9.4, R53.2, R55.2, R57.2, SJ9.2, SJ10.2, TP21.P$1, U25.1, U26.5, U27.S2, U28.S2, U29.5, U30.3
VCC5: C41.1, C43.1, C44.2, C45.1, C46.2, C47.1, C48.1, JP11.4, R65.2, R67.2, R69.2, SJ11.2, SJ12.2, TP26.P$1, U31.1, U32.5, U33.S2, U34.S2, U35.5, U36.3
VCC6: C49.1, C51.1, C52.2, C53.1, C54.2, C55.1, C56.1, JP13.4, R77.2, R79.2, R81.2, SJ13.2, SJ14.2, TP31.P$1, U37.1, U38.5, U39.S2, U40.S2, U41.5, U42.3
VCC7: C57.1, C59.1, C60.2, C61.1, C62.2, C63.1, C64.1, JP15.4, R89.2, R91.2, R93.2, SJ15.2, SJ16.2, TP36.P$1, U43.1, U44.5, U45.S2, U46.S2, U47.5, U48.3
VCC8: C65.1, C67.1, C68.2, C69.1, C70.2, C71.1, C72.1, JP17.4, R101.2, R103.2, R105.2, SJ17.2, SJ18.2, TP41.P$1, U49.1, U50.5, U51.S2, U52.S2, U53.5, U54.3
VCC9: C73.1, C75.1, C76.2, C77.1, C78.2, C79.1, C80.1, JP19.4, R113.2, R115.2, R117.2, SJ19.2, SJ20.2, TP46.P$1, U55.1, U56.5, U57.S2, U58.S2, U59.5, U60.3
VCC10: C81.1, C83.1, C84.2, C85.1, C86.2, C87.1, C88.1, JP21.4, R125.2, R127.2, R129.2, SJ21.2, SJ22.2, TP51.P$1, U61.1, U62.5, U63.S2, U64.S2, U65.5, U66.3
VCC11: C89.1, C91.1, C92.2, C93.1, C94.2, C95.1, C96.1, JP23.4, R137.2, R139.2, R141.2, SJ23.2, SJ24.2, TP56.P$1, U67.1, U68.5, U69.S2, U70.S2, U71.5, U72.3
VCC12: C97.1, C99.1, C100.2, C101.1, C102.2, C103.1, C104.1, JP25.4, R149.2, R151.2, R153.2, SJ25.2, SJ26.2, TP61.P$1, U73.1, U74.5, U75.S2, U76.S2, U77.5, U78.3
VCC13: C105.1, C107.1, C108.2, C109.1, C110.2, C111.1, C112.1, JP27.4, R161.2, R163.2, R165.2, SJ27.2, SJ28.2, TP66.P$1, U79.1, U80.5, U81.S2, U82.S2, U83.5, U84.3
VCC14: C113.1, C115.1, C116.2, C117.1, C118.2, C119.1, C120.1, JP29.4, R173.2, R175.2, R177.2, SJ29.2, SJ30.2, TP71.P$1, U85.1, U86.5, U87.S2, U88.S2, U89.5, U90.3
VCC15: C121.1, C123.1, C124.2, C125.1, C126.2, C127.1, C128.1, JP31.4, R185.2, R187.2, R189.2, SJ31.2, SJ32.2, TP76.P$1, U91.1, U92.5, U93.S2, U94.S2, U95.5, U96.3
VCC16: C129.1, C131.1, C132.2, C133.1, C134.2, C135.1, C136.1, JP33.4, R197.2, R199.2, R201.2, SJ33.2, SJ34.2, TP81.P$1, U97.1, U98.5, U99.S2, U100.S2, U101.5, U102.3
VCC17: C137.1, C139.1, C140.2, C141.1, C142.2, C143.1, C144.1, JP35.4, R209.2, R211.2, R213.2, SJ35.2, SJ36.2, TP86.P$1, U103.1, U104.5, U105.S2, U106.S2, U107.5, U108.3
VCC18: C145.1, C147.1, C148.2, C149.1, C150.2, C151.1, C152.1, JP37.4, R221.2, R223.2, R225.2, SJ37.2, SJ38.2, TP91.P$1, U109.1, U110.5, U111.S2, U112.S2, U113.5, U114.3
VCC19: C153.1, C155.1, C156.2, C157.1, C158.2, C159.1, C160.1, JP39.4, R233.2, R235.2, R237.2, SJ39.2, SJ40.2, TP96.P$1, U115.1, U116.5, U117.S2, U118.S2, U119.5, U120.3

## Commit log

2014-02-21 Added blank schematic
2014-02-21 Created comm ports, LED drivers, and LED receiver in schematic
2014-02-21 Created initial schematic
2014-02-24 Placed components on PCB and started layout
2014-02-24 More progress on layout
2014-02-25 Almost done with layout
2014-02-25 Completed layout. Ready for review before prototype.
2014-02-27 Added trace to DACOUT line. Made test point programming pads smaller. Added extra via on GND plane to beef up current carrying capability.
2014-02-27 Added width measurement on tdocu layer
2014-03-21 Replaced SMD LEDs with PTH. Added PTH Recv'r. Ripped up traces.
2014-03-25 Grouped components in layout
2014-03-25 Initial placement of parts for v02.
2014-03-25 Initial layout complete for v02.
2014-03-26 Reduced board thickness
2014-03-27 Added silk pinout. Ready for v02 review.
2014-03-27 Changed SMT receiver to DNP and removed DNP from PTH receiver and pullup resistor.
2014-03-28 Swapped TX/RX. Added diagonal trace from GND header to pour.
2014-03-31 Removed variant names on IR LEDs in schematic
2014-06-08 Added solder tabs to blinders
2014-06-08 Added second option for SMT IR LEDs. Added solder pads for blinders.
2014-07-30 Created initial library and ability to read X and Z data over I2C.
2014-07-30 Completed I2C Gesture Demo. Added skeleton for I2C Gesture Interrupt demo program.
2014-07-31 Added I2C interrupt capabilities and 2 demo programs to show this.
2014-10-09 Updated REFDES numbers. Changed to v04.
2014-10-09 Moved library to separate repo
2015-01-30 Updated U2, U5, R2. Changed to v05.
2015-02-27 Changed version number. Moved 1 trace. Removed ground pour under part.
2015-03-05 Changed to 1% 10 ohm resistor. Added Arduino I2C address to schematic.
2015-03-05 Added new PDFs of schematic, TOP, and BOT.
2015-03-11 Added name and version to schematic.
2015-03-18 created panel v10
2015-04-22 added bottom side panel fiducials
2015-07-06 Squashed 'Libraries/Arduino/' content from commit f176149
    git-subtree-dir: Libraries/Arduino
    git-subtree-split: f176149d0aae691b364d4957dd376a1141b53abc
2015-07-06 Added .gitattributes and renamed Production files.
2015-07-06 Updated README and LICENSE to new format.
2015-07-06 Fixed link to tag in README
2015-07-06 Removed library
2015-07-06 Squashed 'Libraries/Arduino/' content from commit 96e963c
    git-subtree-dir: Libraries/Arduino
    git-subtree-split: 96e963cafadb52459fd9fc26a9cf7f1abc630121
2015-07-09 Squashed 'Libraries/Arduino/' changes from 96e963c..e6f1c04
    e6f1c04 Fixed typo in library properties file: 'Sensor' to 'Sensors'
    git-subtree-dir: Libraries/Arduino
    git-subtree-split: e6f1c047240c4442af6a2a33c5a980c5d30a480c
2015-07-09 Updated library with fixed typo
2015-07-09 Squashed 'Libraries/Arduino/' changes from e6f1c04..2e7cfa5
    2e7cfa5 Fixed library name and updated README
    5820c58 Fixed library name
    git-subtree-dir: Libraries/Arduino
    git-subtree-split: 2e7cfa53d2a9a545d3d10a0513034204c295d3c1
2015-07-09 Fixed Arduino library name
2015-07-30 Updated GestureSense Logo
2015-07-30 v10a panel gerbers (smaller GTO file)
